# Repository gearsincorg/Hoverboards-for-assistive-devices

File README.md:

### Hoverboards for Assistive Devices (HAD) 
By: Phil Malone

Project page:  https://hackaday.io/project/170932-hoverboards-for-assistive-devices

### Purpose:
The HAD project goal is to enable Hoverboards, or Hoverboard drive components to be re-purposed to provide low-cost mobility for assistive devices.

### Components:
The following components are part of this project:

Hoverboard  This is Hoverboard firmware that supports HUGS (Hoverboard Universal Gateway System).  HUGS is new firmware that is loaded into a hoverboard to replace the tilt-based drive system with a command driven velocity system.  HUGS provides a documented command/response protocol whereby commands can be issued to single or dual drive conteollers.

BluJoy-PCB (Bluetooth Joystick PCB).  BluJoy-PCB is a custom two-part Circuit board with PIC microcontroller and two Bluetooth module.  Once sepparated, the two boards enables the Hoverboard to be controlled by a joystick, over a dedicated Bluetooth interface.  

BluJoy.X (Bluetooth Joystick Firmware). BluJoy.X is a custom MPLAB.X program loaded into the PIC processor on the BluJoy PCB.  It performs automatic Bluetooth pairing, and joystick command transmission.  The firmware currently supports microswitch based joysticks, but will be augmented for Potentiometer based joysticks soon.

HUGS-ESP32 This is developmental code for an ESP32 Dev-kit that was used to test and evaluate the HUGS firmware on the Hoverboard. It connects to a wired joystick to generate commands for both Motor Controllers.  It has been superceeded by the BluJoy PIC firmware which communicates through a single Serial port on the Master Motor Controller.

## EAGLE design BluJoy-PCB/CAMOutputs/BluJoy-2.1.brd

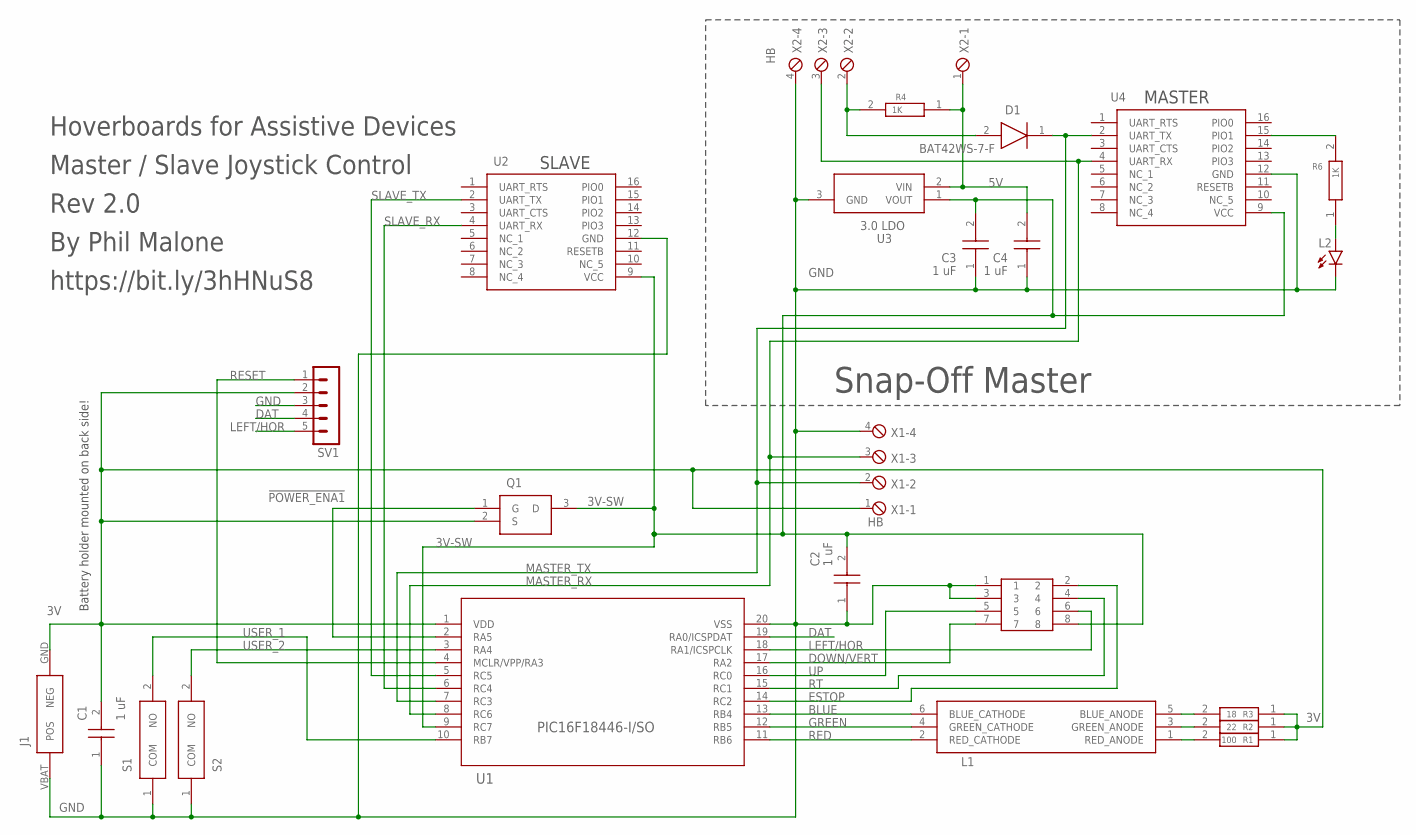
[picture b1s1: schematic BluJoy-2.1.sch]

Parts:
C1, C2, C3, C4: 1 uF; CAPC1608X90N
D1: BAT42WS-7-F; SOD2513X120N
J1: 2468
J2: PHOENIX3.5X8-B; 1751303
L1: ASMB-TTF0-0A20B; ASMBTTF00A20B
L2: LEDCHIP-LED0603; CHIP-LED0603
Q1: P-FET; SOT96P237X111-3N
R1: 100; RESC1608X50N
R2: 22; RESC1608X50N
R3: 18; RESC1608X50N
R4, R6: 1K; RESC1608X50N
S1, S2: PTS636_SK25J_SMTR_LFS; PTS636SK25JSMTRLFS
SV1: PICKIT; MA05-1
U1: PIC16F18446-I/SO; SOIC20_SO_MCH
U2, U4: HM-11; HM-11-MODULE
U3: 3.0 LDO; SOT95P237X112-3N
X1, X2: HB; 4POL254

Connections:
3V: C1.2 (C2), J1.GND (NEG), Q1.2 (S), R1.1, R2.1, R3.1, SV1.2, U1.1 (VDD), X1.1
3V-SW: C2.2 (C2), C3.2 (C2), J2.8, Q1.3 (D), U1.9 (RC7), U2.9 (VCC), U3.1 (VOUT), U4.9 (VCC)
5V: C4.2 (C2), R4.1, U3.2 (VIN), X2.1
!POWER_ENA1: Q1.1 (G), U1.2 (RA5)
BLUE: L1.6 (BLUE_CATHODE), U1.13 (RB4)
DAT: SV1.4, U1.19 (RA0/ICSPDAT)
DOWN/VERT: J2.7, U1.17 (RA2)
ESTOP: J2.2, U1.14 (RC2)
GND: C1.1 (C1), C2.1 (C1), C3.1 (C1), C4.1 (C1), J1.VBAT (POS), J2.1, J2.3, L2.C, S1.1 (COM), S2.1 (COM), SV1.3, U1.20 (VSS), U2.12 (GND), U3.3 (GND), U4.12 (GND), X1.4, X2.4
GREEN: L1.4 (GREEN_CATHODE), U1.12 (RB5)
LEFT/HOR: J2.6, SV1.5, U1.18 (RA1/ICSPCLK)
MASTER_RX: U1.8 (RC6), U4.4 (UART_RX), X1.3, X2.3
MASTER_TX: D1.1 (K), U1.7 (RC3), U4.2 (UART_TX), X1.2
unnamed: D1.2 (A), R4.2, X2.2
unnamed: R6.2, U4.15 (PIO1)
unnamed: L2.A, R6.1
unnamed: L1.1 (RED_ANODE), R1.2
unnamed: L1.3 (GREEN_ANODE), R2.2
unnamed: L1.5 (BLUE_ANODE), R3.2
RED: L1.2 (RED_CATHODE), U1.11 (RB6)
RESET: SV1.1, U1.4 (MCLR/VPP/RA3)
RT: J2.4, U1.15 (RC1)
SLAVE_RX: U1.6 (RC4), U2.4 (UART_RX)
SLAVE_TX: U1.5 (RC5), U2.2 (UART_TX)
UP: J2.5, U1.16 (RC0)
USER_1: S1.2 (NO), U1.10 (RB7)
USER_2: S2.2 (NO), U1.3 (RA4)

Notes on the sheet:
Snap-Off Master
MASTER
SLAVE
Hoverboards for Assistive Devices
Master / Slave Joystick Control
Rev 2.0
By Phil Malone
https://bit.ly/3hHNuS8
Battery holder mounted on back side!

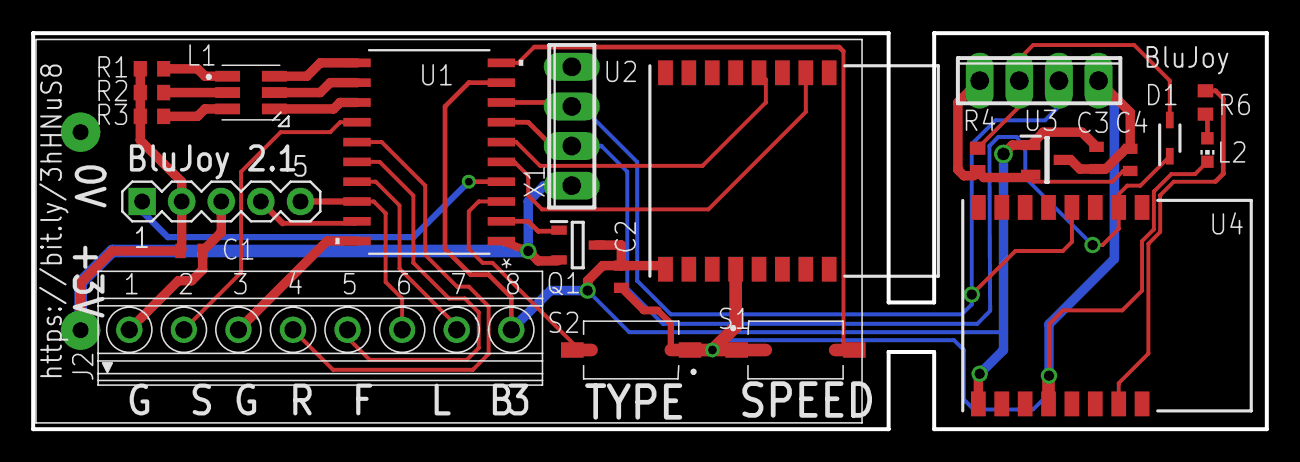
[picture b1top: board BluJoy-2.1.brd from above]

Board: 2 copper layers, 79.1 x 25.4 mm, 24 parts (0 on the bottom side), 27 nets.

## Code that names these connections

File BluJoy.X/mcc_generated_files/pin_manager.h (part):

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// get/set JSLE aliases
#define JSLE_TRIS                 TRISAbits.TRISA1
#define JSLE_LAT                  LATAbits.LATA1
#define JSLE_PORT                 PORTAbits.RA1
#define JSLE_WPU                  WPUAbits.WPUA1
#define JSLE_OD                   ODCONAbits.ODCA1
#define JSLE_ANS                  ANSELAbits.ANSA1
#define JSLE_SetHigh()            do { LATAbits.LATA1 = 1; } while(0)
#define JSLE_SetLow()             do { LATAbits.LATA1 = 0; } while(0)
#define JSLE_Toggle()             do { LATAbits.LATA1 = ~LATAbits.LATA1; } while(0)
#define JSLE_GetValue()           PORTAbits.RA1
#define JSLE_SetDigitalInput()    do { TRISAbits.TRISA1 = 1; } while(0)
#define JSLE_SetDigitalOutput()   do { TRISAbits.TRISA1 = 0; } while(0)
#define JSLE_SetPullup()          do { WPUAbits.WPUA1 = 1; } while(0)
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// get/set JSDO aliases
#define JSDO_TRIS                 TRISAbits.TRISA2
#define JSDO_LAT                  LATAbits.LATA2
#define JSDO_PORT                 PORTAbits.RA2
#define JSDO_WPU                  WPUAbits.WPUA2
#define JSDO_OD                   ODCONAbits.ODCA2
#define JSDO_ANS                  ANSELAbits.ANSA2
#define JSDO_SetHigh()            do { LATAbits.LATA2 = 1; } while(0)
#define JSDO_SetLow()             do { LATAbits.LATA2 = 0; } while(0)
#define JSDO_Toggle()             do { LATAbits.LATA2 = ~LATAbits.LATA2; } while(0)
#define JSDO_GetValue()           PORTAbits.RA2
#define JSDO_SetDigitalInput()    do { TRISAbits.TRISA2 = 1; } while(0)
#define JSDO_SetDigitalOutput()   do { TRISAbits.TRISA2 = 0; } while(0)
#define JSDO_SetPullup()          do { WPUAbits.WPUA2 = 1; } while(0)
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// get/set USER2 aliases
#define USER2_TRIS                 TRISAbits.TRISA4
#define USER2_LAT                  LATAbits.LATA4
#define USER2_PORT                 PORTAbits.RA4
#define USER2_WPU                  WPUAbits.WPUA4
#define USER2_OD                   ODCONAbits.ODCA4
#define USER2_ANS                  ANSELAbits.ANSA4
#define USER2_SetHigh()            do { LATAbits.LATA4 = 1; } while(0)
#define USER2_SetLow()             do { LATAbits.LATA4 = 0; } while(0)
#define USER2_Toggle()             do { LATAbits.LATA4 = ~LATAbits.LATA4; } while(0)
#define USER2_GetValue()           PORTAbits.RA4
#define USER2_SetDigitalInput()    do { TRISAbits.TRISA4 = 1; } while(0)
#define USER2_SetDigitalOutput()   do { TRISAbits.TRISA4 = 0; } while(0)
#define USER2_SetPullup()          do { WPUAbits.WPUA4 = 1; } while(0)
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// get/set POWER_EN aliases
#define POWER_EN_TRIS                 TRISAbits.TRISA5
#define POWER_EN_LAT                  LATAbits.LATA5
#define POWER_EN_PORT                 PORTAbits.RA5
#define POWER_EN_WPU                  WPUAbits.WPUA5
#define POWER_EN_OD                   ODCONAbits.ODCA5
#define POWER_EN_ANS                  ANSELAbits.ANSA5
#define POWER_EN_SetHigh()            do { LATAbits.LATA5 = 1; } while(0)
#define POWER_EN_SetLow()             do { LATAbits.LATA5 = 0; } while(0)
#define POWER_EN_Toggle()             do { LATAbits.LATA5 = ~LATAbits.LATA5; } while(0)
#define POWER_EN_GetValue()           PORTAbits.RA5
#define POWER_EN_SetDigitalInput()    do { TRISAbits.TRISA5 = 1; } while(0)
#define POWER_EN_SetDigitalOutput()   do { TRISAbits.TRISA5 = 0; } while(0)
#define POWER_EN_SetPullup()          do { WPUAbits.WPUA5 = 1; } while(0)
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// get/set BLUE aliases
#define BLUE_TRIS                 TRISBbits.TRISB4
#define BLUE_LAT                  LATBbits.LATB4
#define BLUE_PORT                 PORTBbits.RB4
#define BLUE_WPU                  WPUBbits.WPUB4
#define BLUE_OD                   ODCONBbits.ODCB4
#define BLUE_ANS                  ANSELBbits.ANSB4
#define BLUE_SetHigh()            do { LATBbits.LATB4 = 1; } while(0)
#define BLUE_SetLow()             do { LATBbits.LATB4 = 0; } while(0)
#define BLUE_Toggle()             do { LATBbits.LATB4 = ~LATBbits.LATB4; } while(0)
#define BLUE_GetValue()           PORTBbits.RB4
#define BLUE_SetDigitalInput()    do { TRISBbits.TRISB4 = 1; } while(0)
#define BLUE_SetDigitalOutput()   do { TRISBbits.TRISB4 = 0; } while(0)
#define BLUE_SetPullup()          do { WPUBbits.WPUB4 = 1; } while(0)
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// get/set GREEN aliases
#define GREEN_TRIS                 TRISBbits.TRISB5
#define GREEN_LAT                  LATBbits.LATB5
#define GREEN_PORT                 PORTBbits.RB5
#define GREEN_WPU                  WPUBbits.WPUB5
#define GREEN_OD                   ODCONBbits.ODCB5
#define GREEN_ANS                  ANSELBbits.ANSB5
#define GREEN_SetHigh()            do { LATBbits.LATB5 = 1; } while(0)
#define GREEN_SetLow()             do { LATBbits.LATB5 = 0; } while(0)
#define GREEN_Toggle()             do { LATBbits.LATB5 = ~LATBbits.LATB5; } while(0)
#define GREEN_GetValue()           PORTBbits.RB5
#define GREEN_SetDigitalInput()    do { TRISBbits.TRISB5 = 1; } while(0)
#define GREEN_SetDigitalOutput()   do { TRISBbits.TRISB5 = 0; } while(0)
#define GREEN_SetPullup()          do { WPUBbits.WPUB5 = 1; } while(0)
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// get/set RED aliases
#define RED_TRIS                 TRISBbits.TRISB6
#define RED_LAT                  LATBbits.LATB6
#define RED_PORT                 PORTBbits.RB6
#define RED_WPU                  WPUBbits.WPUB6
#define RED_OD                   ODCONBbits.ODCB6
#define RED_ANS                  ANSELBbits.ANSB6
#define RED_SetHigh()            do { LATBbits.LATB6 = 1; } while(0)
#define RED_SetLow()             do { LATBbits.LATB6 = 0; } while(0)
#define RED_Toggle()             do { LATBbits.LATB6 = ~LATBbits.LATB6; } while(0)
#define RED_GetValue()           PORTBbits.RB6
#define RED_SetDigitalInput()    do { TRISBbits.TRISB6 = 1; } while(0)
#define RED_SetDigitalOutput()   do { TRISBbits.TRISB6 = 0; } while(0)
#define RED_SetPullup()          do { WPUBbits.WPUB6 = 1; } while(0)
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// get/set USER1 aliases
#define USER1_TRIS                 TRISBbits.TRISB7
#define USER1_LAT                  LATBbits.LATB7
#define USER1_PORT                 PORTBbits.RB7
#define USER1_WPU                  WPUBbits.WPUB7
#define USER1_OD                   ODCONBbits.ODCB7
#define USER1_ANS                  ANSELBbits.ANSB7
#define USER1_SetHigh()            do { LATBbits.LATB7 = 1; } while(0)
#define USER1_SetLow()             do { LATBbits.LATB7 = 0; } while(0)
#define USER1_Toggle()             do { LATBbits.LATB7 = ~LATBbits.LATB7; } while(0)
#define USER1_GetValue()           PORTBbits.RB7
#define USER1_SetDigitalInput()    do { TRISBbits.TRISB7 = 1; } while(0)
#define USER1_SetDigitalOutput()   do { TRISBbits.TRISB7 = 0; } while(0)
#define USER1_SetPullup()          do { WPUBbits.WPUB7 = 1; } while(0)
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// get/set JSUP aliases
#define JSUP_TRIS                 TRISCbits.TRISC0
#define JSUP_LAT                  LATCbits.LATC0
#define JSUP_PORT                 PORTCbits.RC0
#define JSUP_WPU                  WPUCbits.WPUC0
#define JSUP_OD                   ODCONCbits.ODCC0
#define JSUP_ANS                  ANSELCbits.ANSC0
#define JSUP_SetHigh()            do { LATCbits.LATC0 = 1; } while(0)
#define JSUP_SetLow()             do { LATCbits.LATC0 = 0; } while(0)
#define JSUP_Toggle()             do { LATCbits.LATC0 = ~LATCbits.LATC0; } while(0)
#define JSUP_GetValue()           PORTCbits.RC0
#define JSUP_SetDigitalInput()    do { TRISCbits.TRISC0 = 1; } while(0)
#define JSUP_SetDigitalOutput()   do { TRISCbits.TRISC0 = 0; } while(0)
#define JSUP_SetPullup()          do { WPUCbits.WPUC0 = 1; } while(0)
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// get/set JSRI aliases
#define JSRI_TRIS                 TRISCbits.TRISC1
#define JSRI_LAT                  LATCbits.LATC1
#define JSRI_PORT                 PORTCbits.RC1
#define JSRI_WPU                  WPUCbits.WPUC1
#define JSRI_OD                   ODCONCbits.ODCC1
#define JSRI_ANS                  ANSELCbits.ANSC1
#define JSRI_SetHigh()            do { LATCbits.LATC1 = 1; } while(0)
#define JSRI_SetLow()             do { LATCbits.LATC1 = 0; } while(0)
#define JSRI_Toggle()             do { LATCbits.LATC1 = ~LATCbits.LATC1; } while(0)
#define JSRI_GetValue()           PORTCbits.RC1
#define JSRI_SetDigitalInput()    do { TRISCbits.TRISC1 = 1; } while(0)
#define JSRI_SetDigitalOutput()   do { TRISCbits.TRISC1 = 0; } while(0)
#define JSRI_SetPullup()          do { WPUCbits.WPUC1 = 1; } while(0)
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// get/set JSBU aliases
#define JSBU_TRIS                 TRISCbits.TRISC2
#define JSBU_LAT                  LATCbits.LATC2
#define JSBU_PORT                 PORTCbits.RC2
#define JSBU_WPU                  WPUCbits.WPUC2
#define JSBU_OD                   ODCONCbits.ODCC2
#define JSBU_ANS                  ANSELCbits.ANSC2
#define JSBU_SetHigh()            do { LATCbits.LATC2 = 1; } while(0)
#define JSBU_SetLow()             do { LATCbits.LATC2 = 0; } while(0)
#define JSBU_Toggle()             do { LATCbits.LATC2 = ~LATCbits.LATC2; } while(0)
#define JSBU_GetValue()           PORTCbits.RC2
#define JSBU_SetDigitalInput()    do { TRISCbits.TRISC2 = 1; } while(0)
#define JSBU_SetDigitalOutput()   do { TRISCbits.TRISC2 = 0; } while(0)
#define JSBU_SetPullup()          do { WPUCbits.WPUC2 = 1; } while(0)
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// get/set M_RX aliases
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
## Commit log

2020-08-14 Update Readme's
2020-08-14 Added Cad models for HB 1/4 20 Mounting
2020-09-02 Updated Pairing
    New LED colors
    Clearing Bluetooth IDs during Pairing
2020-10-05 Hackaday Prize Release.
    Latest Firmware, Software, PCB and Cad.
2020-10-14 Added HUGS-ESP32 firmware to Repo.
    HUGS-ESP32 was used for development and testing of the Hoverboard Firmware, but has been superceeded by the opperational BluJoy code.
2021-03-15 ignore platformio dir
2021-03-15 copy maxgerhardt's platformio changes
2021-03-15 Work around gcc bug
2021-06-13 Added single serial port interface
    Added serial processing on debug Coms port.
    Accepts new Dual Speed command DSPE For left and right motor.
2021-06-13 Updated GigaDevice Libraries (3.2)

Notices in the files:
BluJoy.X/mcc_generated_files/pin_manager.h:
(c) 2018 Microchip Technology Inc. and its subsidiaries.
parts and their libraries:
COPYRIGHT: Copyright (C) 2018 Accelerated Designs. All rights reserved
